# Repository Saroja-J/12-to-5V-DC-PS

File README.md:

## 12V-5V DC Power Supply
### Overview
   This circuit converts an unregulated 12V DC input into a regulated 5V DC output using a 7805 linear voltage regulator. The 7805 is a 3 terminal IC that maintains a constant 5V output even if input voltage or load current varies. I/P capacitor C1 noise/ripples from the 12V source while output capacitor C2 stabilizes the 5V and improves transient response. LED acts as a power indicator. This design is simple,cheap and reliable for low-current 5V circuits.
### Working
Input - 12V dc enters through input terminal and capacitor C1 filters the noise/ripples.
Regulation - 7805 drops excess voltage as heat and provide 5V at output.
Output - C2 removes high frequency noise and provide stable %V at output.
### Hardware specification
Barrel_Jack - I/P connector for 12V input
C1 capacitor(100uf/25V) - I/P filter
U1 L7805 - Linear regulator, provides 5V/1A at output terminal
C2 capacitor(10uf/16v) - O/P filter
R1 resistror(460 ohms) - current limiting resistor for LED
LED1 - Power Indicator
J2 connector - Output terminal
### Features
* Fixed 5V Regulated Output from 7V-35V input.
* Overload protection
* simple 3 pin interface
### Applications
-Microcontroller board, sensor module,Logic circuits likewise where there is a requirement of 5V stable Dc voltage. 
### NOTE
* Minimum 7V needs to be provided at the input to get stable 5V at output
* For 200mA< load current require proper HeatSink.

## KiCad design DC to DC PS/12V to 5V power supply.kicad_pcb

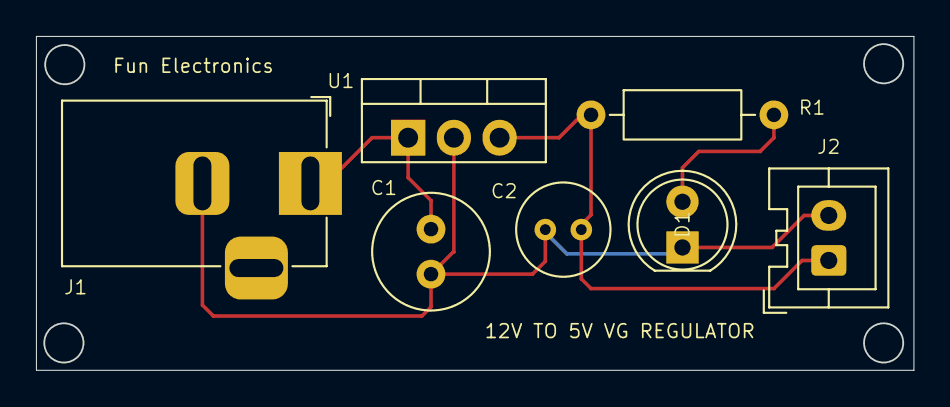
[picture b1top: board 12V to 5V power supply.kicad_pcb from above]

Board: 2 copper layers, 48.7 x 18.5 mm, 7 parts (0 on the bottom side), 4 nets.

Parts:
C1=100uf/25V1: C_US; C_Radial_D6.3mm_H11.0mm_P2.50mm
C2=10uf/16V1: C_US; C_Radial_D5.0mm_H5.0mm_P2.00mm
D1: LED; LED_D5.0mm
J1: Barrel_Jack_Switch; BarrelJack_Horizontal
J2: Conn_01x02_Pin; JST_XA_B02B-XASK-1_1x02_P2.50mm_Vertical
R1: R=220; R_Axial_DIN0207_L6.3mm_D2.5mm_P10.16mm_Horizontal
U1: L7805; TO-220-3_Vertical

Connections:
+5V: C2=10uf/16V1.1, J2.1, R1.1, U1.3 (OUT)
+12V: C1=100uf/25V1.1, J1.1, U1.1 (IN)
GND: C1=100uf/25V1.2, C2=10uf/16V1.2, D1.1 (K), J1.2, J2.2, U1.2 (GND)
unnamed: D1.2 (A), R1.2
